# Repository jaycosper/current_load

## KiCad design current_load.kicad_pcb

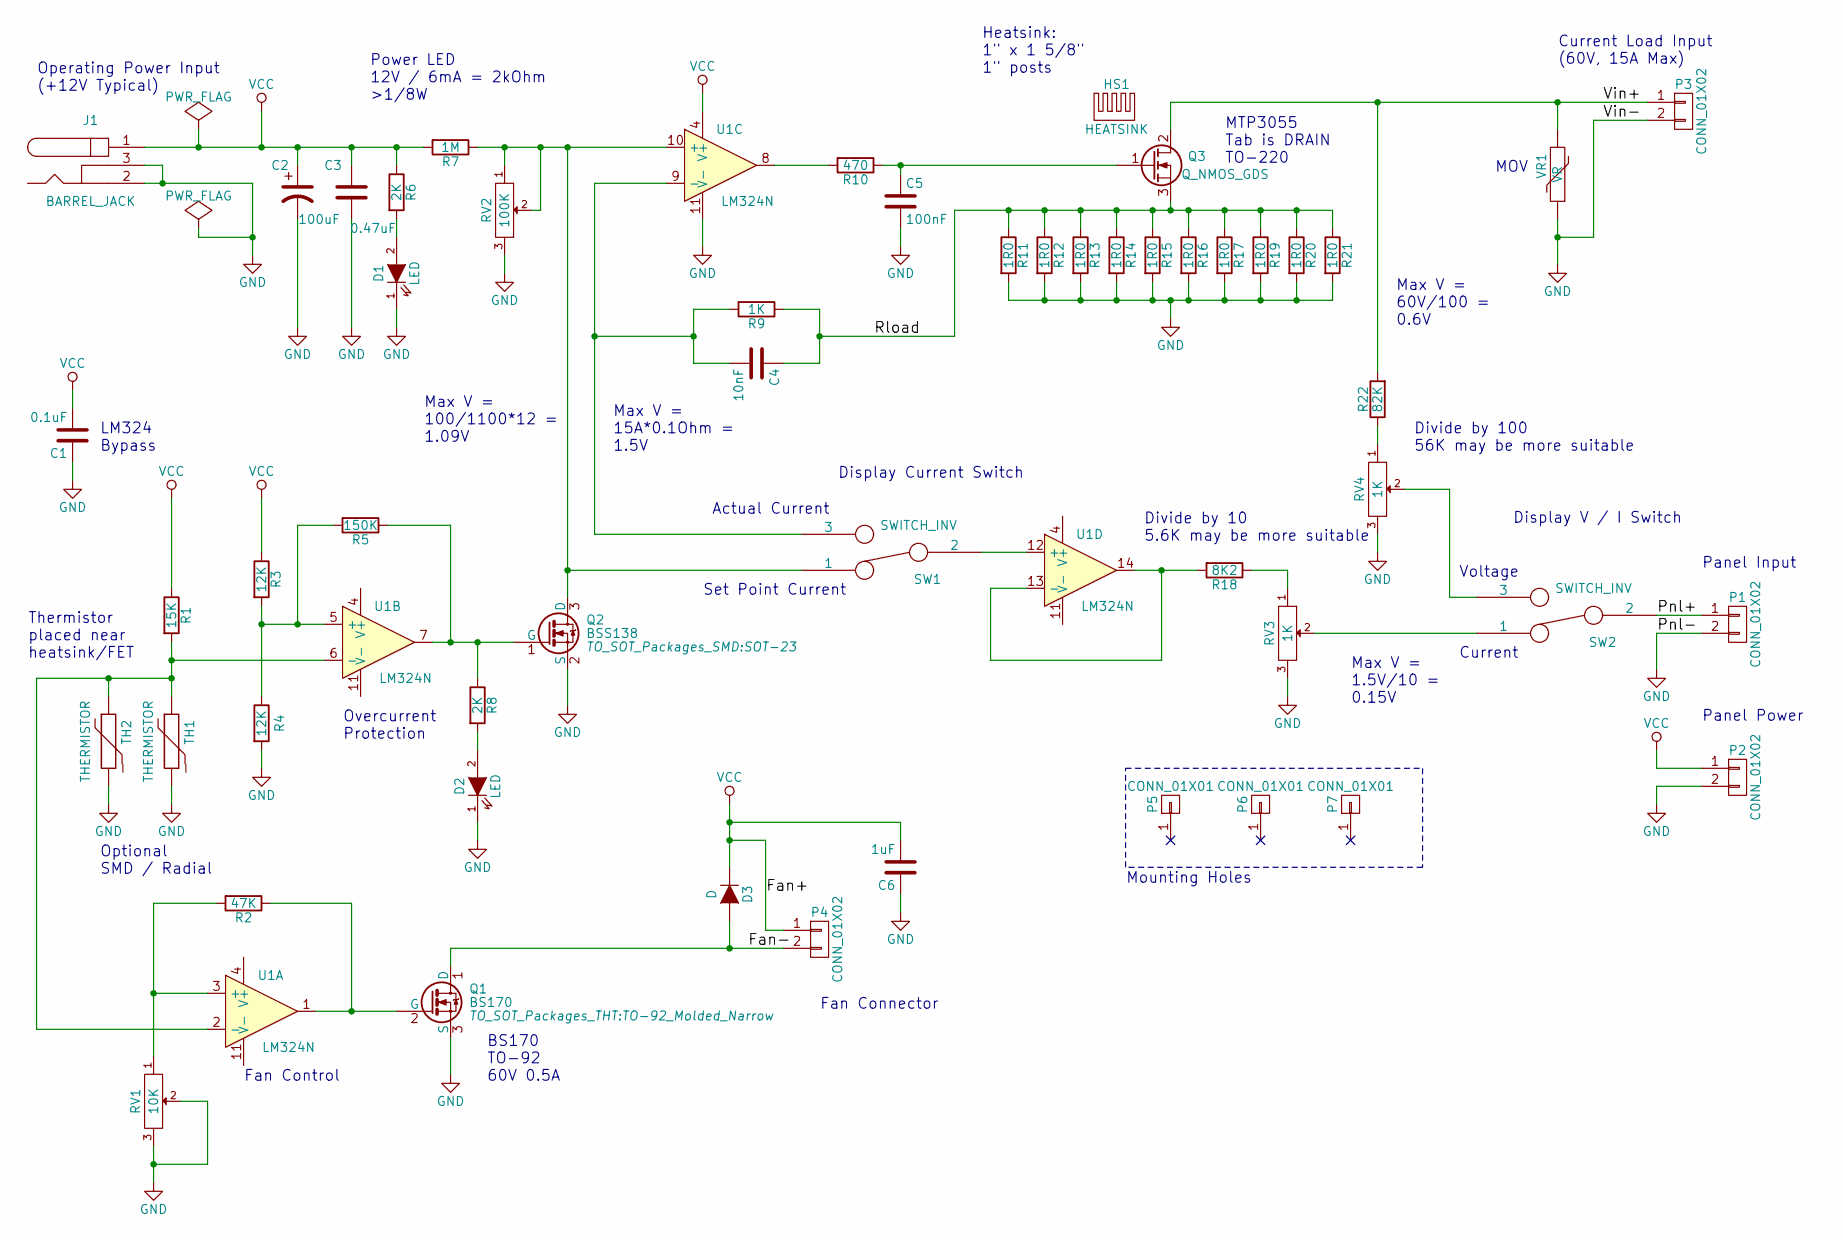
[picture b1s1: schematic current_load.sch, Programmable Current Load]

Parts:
C1: 0.1uF; C_0805_HandSoldering
C2: 100uF; C_1210_HandSoldering
C3: 0.47uF; C_0805_HandSoldering
C4: 10nF; C_0805_HandSoldering
C5: 100nF; C_0805_HandSoldering
C6: 1uF; C_0805_HandSoldering
D1, D2: LED; LED_D5.0mm
D3: D; DO-214AC
HS1: HEATSINK; heatsink_aavid5299
J1: BARREL_JACK
P1, P2, P4: CONN_01X02; Pin_Header_Straight_1x02_Pitch2.54mm
P3: CONN_01X02; SolderWirePad_2x_2mmDrill
P5, P6, P7: CONN_01X01; MountingHole_4.3mm_M4
Q1: BS170; TO-92_Molded_Narrow
Q2: BSS138; SOT-23
Q3: Q_NMOS_GDS; TO-220_Neutral123_Vertical
R1: 15K; R_0805_HandSoldering
R2: 47K; R_0805_HandSoldering
R3, R4: 12K; R_0805_HandSoldering
R5: 150K; R_0805_HandSoldering
R6, R8: 2K; R_0805_HandSoldering
R7: 1M; R_0805_HandSoldering
R9: 1K; R_0805_HandSoldering
R10: 470; R_0805_HandSoldering
R11, R12, R13, R14, R15, R16, R17, R19, R20, R21: 1R0; R_Axial_DIN0414_L11.9mm_D4.5mm_P5.08mm_Vertical
R18: 8K2; R_0805_HandSoldering
R22: 82K; R_0805_HandSoldering
RV1: 10K; TT_23BRxxxLFTR_Trimmer
RV2: 100K; Pin_Header_Straight_1x03_Pitch2.54mm
RV3, RV4: 1K; TT_23BRxxxLFTR_Trimmer
SW1, SW2: SWITCH_INV; Pin_Header_Straight_1x03_Pitch2.54mm
TH1: THERMISTOR; C_Disc_D3.0mm_W2.0mm_P2.50mm
TH2: THERMISTOR; R_0805_HandSoldering
U1: LM324N; SOIC-14_3.9x8.7mm_Pitch1.27mm
VR1: VR; R_Radial_Power_L11.0mm_W7.0mm_P5.00mm

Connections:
/Fan-: D3.2 (A), P4.2, Q1.1 (D)
/Pnl+: P1.1, SW2.2
/Rload: C4.1, Q3.3 (S), R9.1, R11.1, R12.1, R13.1, R14.1, R15.1, R16.1, R17.1, R19.1, R20.1, R21.1
/Vin+: P3.1, Q3.2 (D), R22.2, VR1.2
GND: C1.1, C2.2, C3.1, C5.2, C6.1, D1.1 (K), D2.1 (K), J1.2, J1.3, P1.2, P2.2, P3.2, Q1.3 (S), Q2.2 (S), R4.2, R11.2, R12.2, R13.2, R14.2, R15.2, R16.2, R17.2, R19.2, R20.2, R21.2, RV1.2, RV1.3, RV2.3, RV3.3, RV4.3, TH1.2, TH2.2, U1.11 (V-), VR1.1
unnamed: C4.2, R9.2, SW1.3, U1.9 (-)
unnamed: C5.1, Q3.1 (G), R10.1
unnamed: D1.2 (A), R6.2
unnamed: D2.2 (A), R8.2
unnamed: Q1.2 (G), R2.1, U1.1
unnamed: Q2.1 (G), R5.1, R8.1, U1.7
unnamed: Q2.3 (D), R7.1, RV2.1, RV2.2, SW1.1, U1.10 (+)
unnamed: R1.2, TH1.1, TH2.1, U1.2 (-), U1.6 (-)
unnamed: R2.2, RV1.1, U1.3 (+)
unnamed: R3.2, R4.1, R5.2, U1.5 (+)
unnamed: R10.2, U1.8
unnamed: R18.1, RV3.1
unnamed: R18.2, U1.13 (-), U1.14
unnamed: R22.1, RV4.1
unnamed: RV3.2, SW2.1
unnamed: RV4.2, SW2.3
unnamed: SW1.2, U1.12 (+)
VCC: C1.2, C2.1, C3.2, C6.2, D3.1 (K), J1.1, P2.1, P4.1, R1.1, R3.1, R6.1, R7.2, U1.4 (V+)

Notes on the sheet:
MTP3055 Tab is DRAIN TO-220
Power LED 12V / 6mA = 2kOhm >1/8W
LM324 Bypass
Operating Power Input (+12V Typical)
MOV
Actual Current
Set Point Current
Display Current Switch
Current Load Input (60V, 15A Max)
Display V / I Switch
Voltage
Current
Overcurrent Protection
Fan Control
Fan Connector
Heatsink: 1" x 1 5/8" 1" posts
Thermistor placed near heatsink/FET
BS170 TO-92 60V 0.5A
Divide by 10 5.6K may be more suitable
Divide by 100 56K may be more suitable
Mounting Holes
Max V = 100/1100*12 = 1.09V
Max V = 15A*0.1Ohm = 1.5V
Max V = 1.5V/10 = 0.15V
Max V = 60V/100 = 0.6V
Panel Input
Panel Power
Optional SMD / Radial

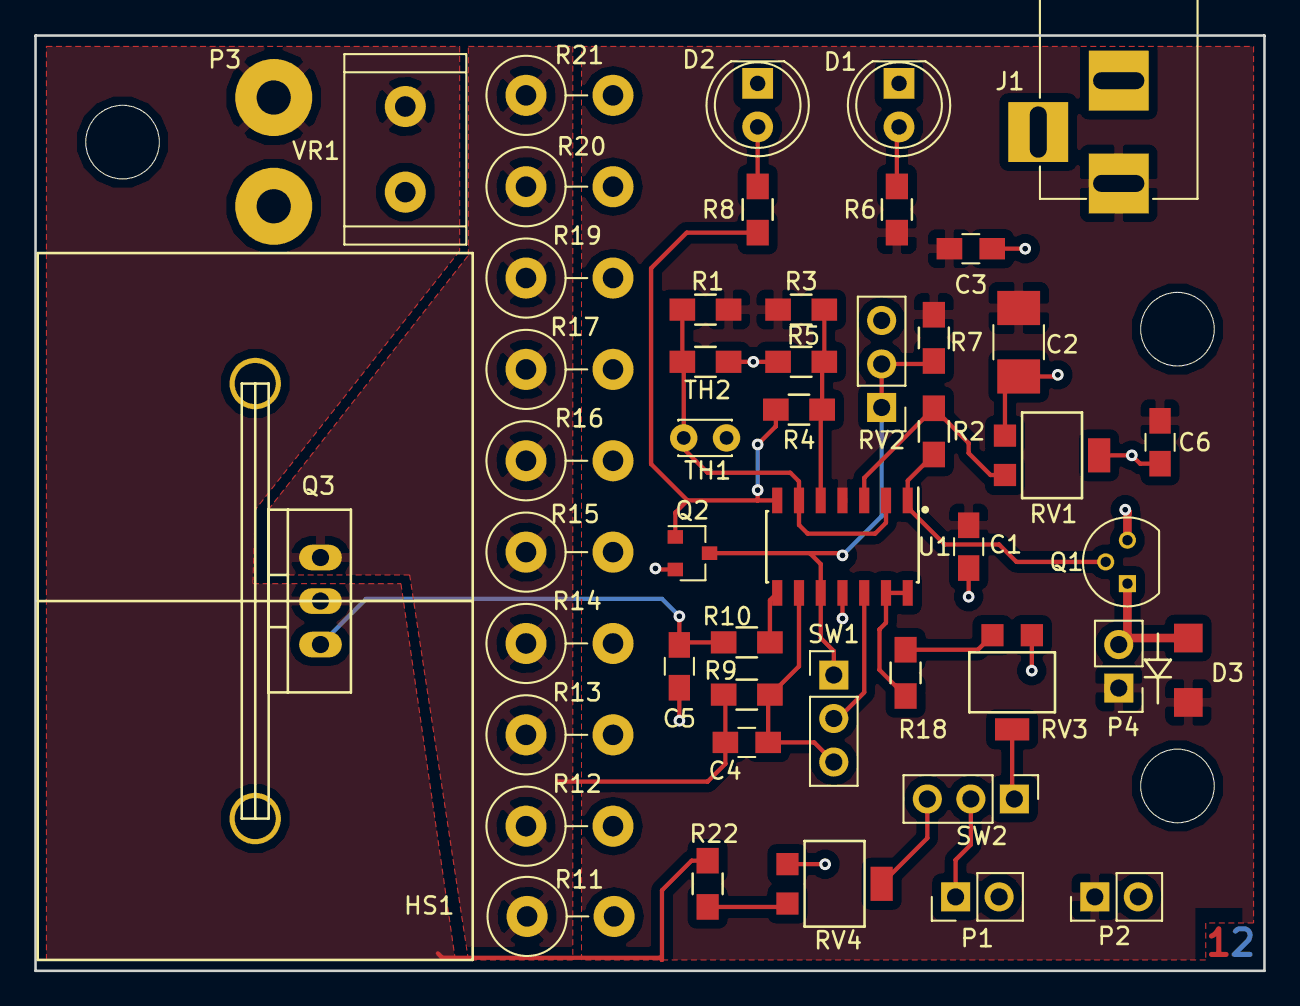
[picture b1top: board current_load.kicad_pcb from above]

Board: 2 copper layers, 71.8 x 54.6 mm, 53 parts (0 on the bottom side), 23 nets.
